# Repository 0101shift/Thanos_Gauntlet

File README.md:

# Thanos_Gauntlet
Thanos Gauntlet is an e-Badge design inspired by Thanos Gauntlet, this e-Badge integrates Capacitive touch sensor & an Attiny45 controller for LED control. when edges of the board is touched, Gauntlet light's up and fades away gradually. The RGB LEDs are reverse mounted below each stone and the whole badge is powered from a 3V coin cell.

NOTE: BC547 pinout used in the design won't support SOT23 package, you may have to do some rework with TO-92 package.

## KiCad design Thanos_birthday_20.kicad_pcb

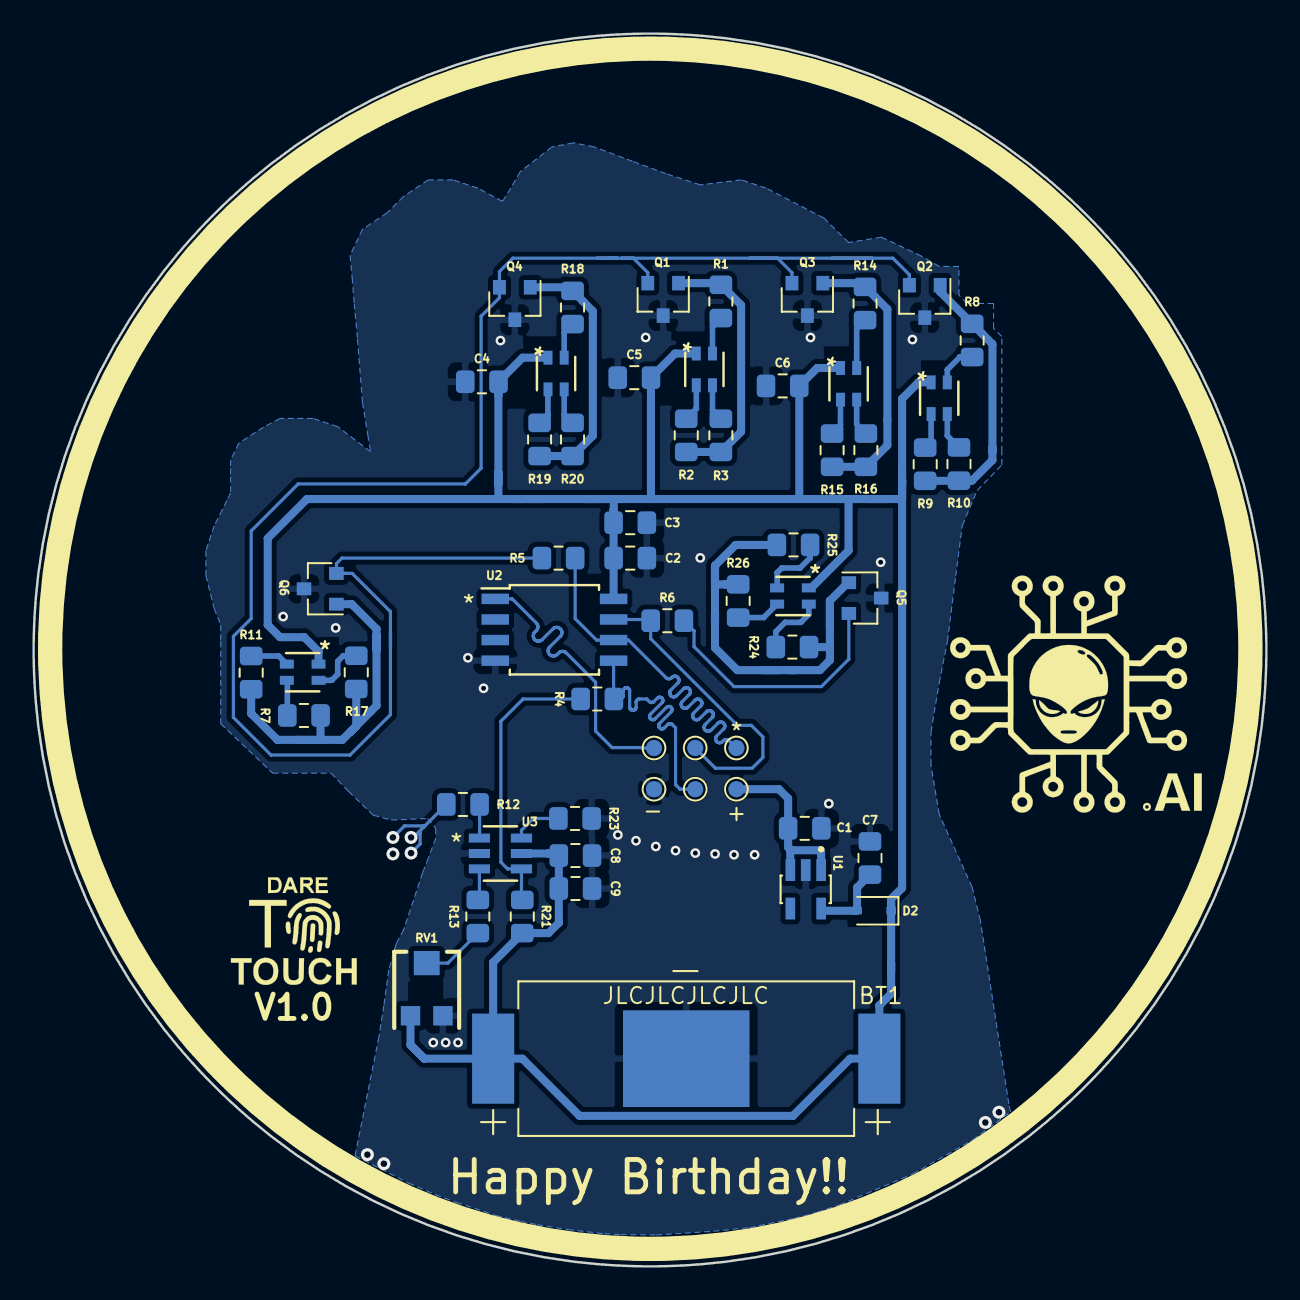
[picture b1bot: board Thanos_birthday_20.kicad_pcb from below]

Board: 2 copper layers, 76.0 x 76.0 mm, 58 parts (58 on the bottom side), 39 nets.

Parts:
BT1: BC-2003; BAT_BC-2003
C1, C7, C8: 1uF; C_0805_2012Metric_Pad1.15x1.40mm_HandSolder
C2: 4.7uF; C_0805_2012Metric_Pad1.15x1.40mm_HandSolder
C3, C9: 0.1uF; C_0805_2012Metric_Pad1.15x1.40mm_HandSolder
C4, C5, C6: 10uF; C_0805_2012Metric_Pad1.15x1.40mm_HandSolder
D2: D_Schottky; D_SOD-323
LED1, LED2, LED3, LED4, LED5, LED6: ASMB-LTB2-0A333; ASMB_LTB2_0A333_PLCC4_Reverse_Mount
Q1, Q2, Q3, Q4, Q5, Q6: BC547; SOT-23
R1, R2, R3, R7, R8, R9, R10, R11, R14, R15, R16, R17, R18, R19, R20, R24, R25, R26: R; R_0805_2012Metric_Pad1.15x1.40mm_HandSolder
R4, R5, R6, R13, R21, R23: 10K; R_0805_2012Metric_Pad1.15x1.40mm_HandSolder
R12: 4.7K; R_0805_2012Metric_Pad1.15x1.40mm_HandSolder
RV1: 10K; TC33X-2-103E
TP1, TP2, TP3, TP4, TP5, TP6: TestPoint; TestPoint_Pad_D1.0mm
U1: AP2112K-3.3TRG1
U2: ATtiny85-20SU; SOIJ-8_5.3x5.3mm_P1.27mm
U3: MTCH101T-I_OT; MTCH101T

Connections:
/5V_in: C1.1, TP5.1, U1.1, U1.3
/BIG_LED: Q5.2, R6.1
/LED_OUT: Q1.2, Q2.2, Q3.2, Q4.2, Q6.2, R5.1
/MISO: R5.2, TP2.1, U2.6
/MOSI: R4.2, TP3.1, U2.5
/MTO: R4.1, R21.2, U3.4
/MTPM: R23.1, U3.6
/MTSA: R13.1, RV1.2
/SCK: R6.2, TP4.1, U2.7
/Vin: BT1.S1+, BT1.S2+, C2.1, C3.1, C4.1, C5.1, C6.1, C8.1, C9.1, D2.1, LED1.1, LED2.1, LED3.1, LED4.1, LED5.1, LED6.1, R21.1, RV1.1, U2.8, U3.5
/rst: TP1.1, U2.1
GND: BT1.-, C1.2, C2.2, C3.2, C4.2, C5.2, C6.2, C7.2, C8.2, C9.2, Q1.3, Q2.3, Q3.3, Q4.3, Q5.3, Q6.3, R23.2, RV1.3, TP6.1, U1.2, U2.4, U3.2
unnamed: C7.1, D2.2, U1.5
unnamed: LED1.2, R1.1
unnamed: LED1.3, R3.1
unnamed: LED1.4, R2.1
unnamed: LED2.2, R8.1
unnamed: LED2.3, R10.1
unnamed: LED2.4, R9.1
unnamed: LED3.2, R14.1
unnamed: LED3.3, R16.1
unnamed: LED3.4, R15.1
unnamed: LED4.2, R18.1
unnamed: LED4.3, R20.1
unnamed: LED4.4, R19.1
unnamed: LED5.2, R24.1
unnamed: LED5.3, R26.1
unnamed: LED5.4, R25.1
unnamed: LED6.2, R17.1
unnamed: LED6.3, R7.1
unnamed: LED6.4, R11.1
unnamed: Q1.1, R1.2, R2.2, R3.2
unnamed: Q2.1, R8.2, R9.2, R10.2
unnamed: Q3.1, R14.2, R15.2, R16.2
unnamed: Q4.1, R18.2, R19.2, R20.2
unnamed: Q5.1, R24.2, R25.2, R26.2
unnamed: Q6.1, R7.2, R11.2, R17.2
unnamed: R12.1, U3.1
unnamed: R13.2, U3.3

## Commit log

2021-07-04 Add files via upload
    Added Thanos Gauntlet SCH, PCB and Gerber files
2022-06-18 Update README.md
    Added Image
2022-06-18 Update README.md
    Added Image and updated README
2022-06-18 Add files via upload
    Added project design file
2022-06-20 Add files via upload
    Added Design in .pdf format

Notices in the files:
parts and their libraries:
Copyright 2016 Accelerated Designs. All rights reserved.
